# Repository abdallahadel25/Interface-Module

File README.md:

# Interface-Module

The module an Attiny 1614 based that is used to act as an intefcae between a micro-controller and another module whatever its interface protocal it provides casting from :

  1- SPI
  2- I2C
  3- UART
  4- 4*DIGITAL SIGNALS
  5- 4*ANALOG SIGNALS

  Schematic and PCB are designed using Eagle

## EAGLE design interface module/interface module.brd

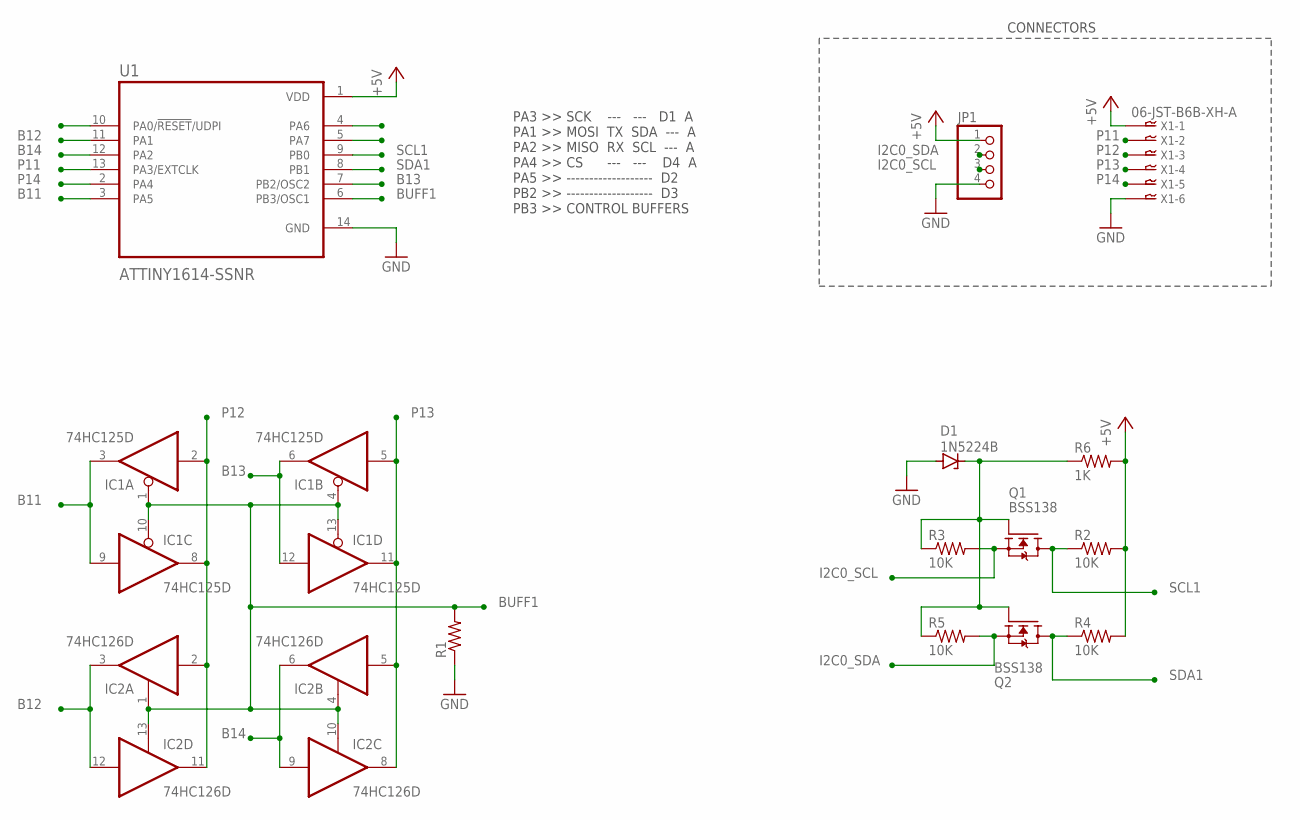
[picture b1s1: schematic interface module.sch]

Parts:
D1: 1N5224B; DO34Z7
IC1: 74HC125D; SO14
IC2: 74HC126D; SO14
JP1: PINHD-1X4; 1X04
Q1, Q2: BSS138; SOT95P240X111-3N
R1: R-US_R0805; R0805
R2, R3, R4, R5: 10K; R0805
R6: 1K; R0805
U1: ATTINY1614-SSNR; SOIC127P600X175-14N
X1: 06-JST-B6B-XH-A; B6B-XH

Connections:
+5V: JP1.1, R2.2, R4.2, R6.2, U1.1 (VDD), X1.P$1
B11: IC1.3 (O), IC1.9 (I), U1.3 (PA5)
B12: IC2.3 (O), IC2.12 (I), U1.11 (PA1)
B13: IC1.6 (O), IC1.12 (I), U1.7 (PB2/OSC2)
B14: IC2.6 (O), IC2.9 (I), U1.12 (PA2)
BUFF1: IC1.1 (OE), IC1.4 (OE), IC1.10 (OE), IC1.13 (OE), IC2.1 (OE), IC2.4 (OE), IC2.10 (OE), IC2.13 (OE), R1.2, U1.6 (PB3/OSC1)
GND: D1.A, IC1.7 (GND), IC2.7 (GND), JP1.4, R1.1, U1.14 (GND), X1.P$6
I2C0_SCL: JP1.3, Q1.2 (S), R3.2
I2C0_SDA: JP1.2, Q2.2 (S), R5.2
unnamed: D1.C, Q1.1 (G), Q2.1 (G), R3.1, R5.1, R6.1
P11: U1.13 (PA3/EXTCLK), X1.P$2
P12: IC1.2 (I), IC1.8 (O), IC2.2 (I), IC2.11 (O), X1.P$3
P13: IC1.5 (I), IC1.11 (O), IC2.5 (I), IC2.8 (O), X1.P$4
P14: U1.2 (PA4), X1.P$5
SCL1: Q1.3 (D), R2.1, U1.9 (PB0)
SDA1: Q2.3 (D), R4.1, U1.8 (PB1)
VCC: IC1.14 (VCC), IC2.14 (VCC)

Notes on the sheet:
PA3 >> SCK --- --- D1 A PA1 >> MOSI TX SDA --- A PA2 >> MISO RX SCL --- A PA4 >> CS --- --- D4 A PA5 >> ------------------- D2 PB2 >> ------------------- D3 PB3 >> CONTROL BUFFERS
CONNECTORS

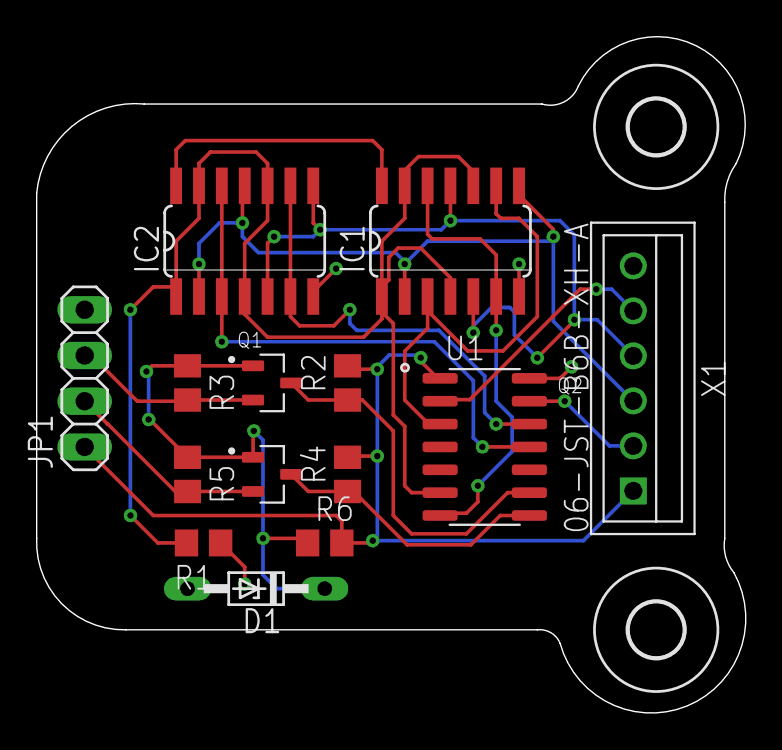
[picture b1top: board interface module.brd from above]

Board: 2 copper layers, 39.4 x 37.6 mm, 16 parts (0 on the bottom side), 17 nets.

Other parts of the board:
U$1, U$2: 3,0

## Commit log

2022-11-16 Create LICENCE
